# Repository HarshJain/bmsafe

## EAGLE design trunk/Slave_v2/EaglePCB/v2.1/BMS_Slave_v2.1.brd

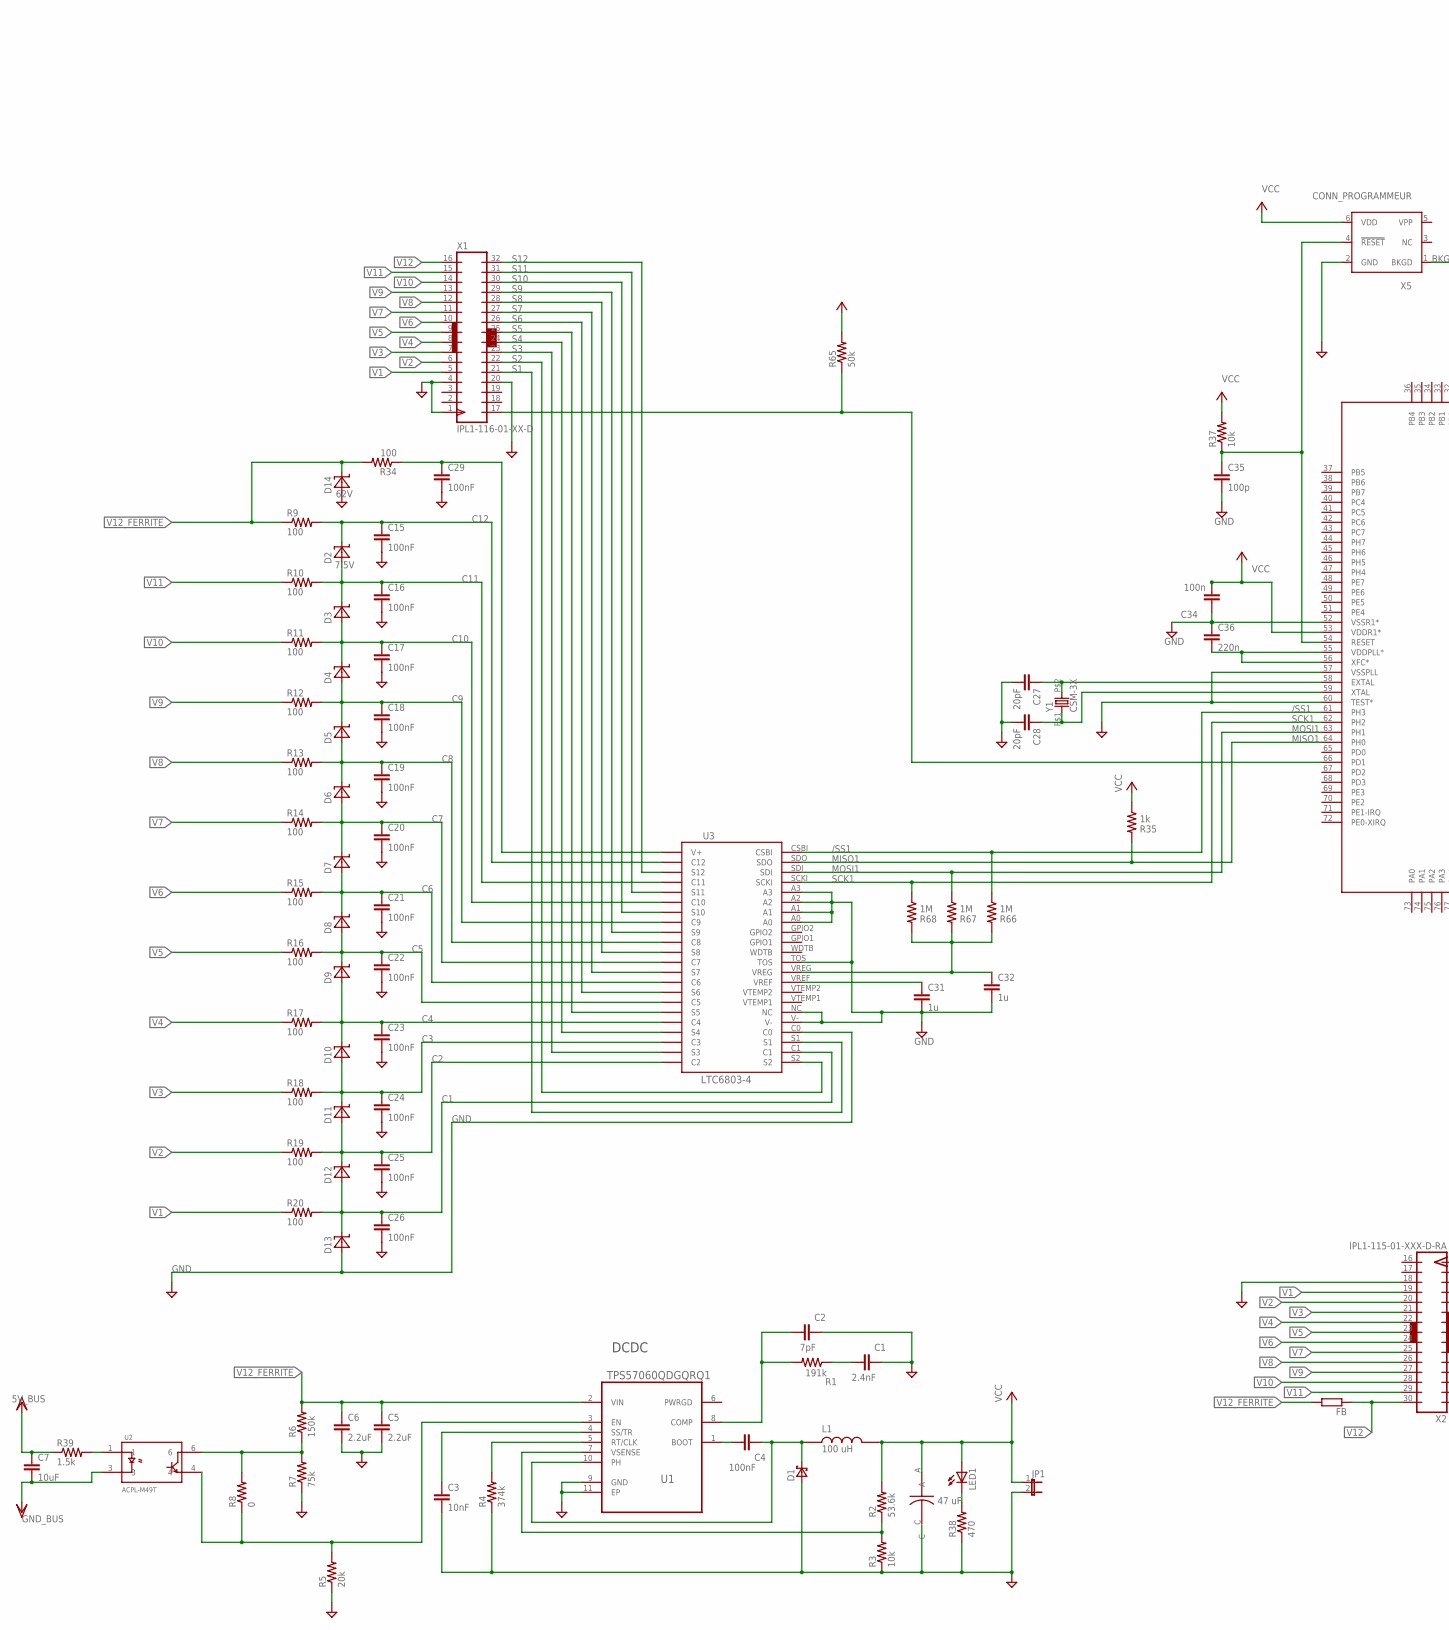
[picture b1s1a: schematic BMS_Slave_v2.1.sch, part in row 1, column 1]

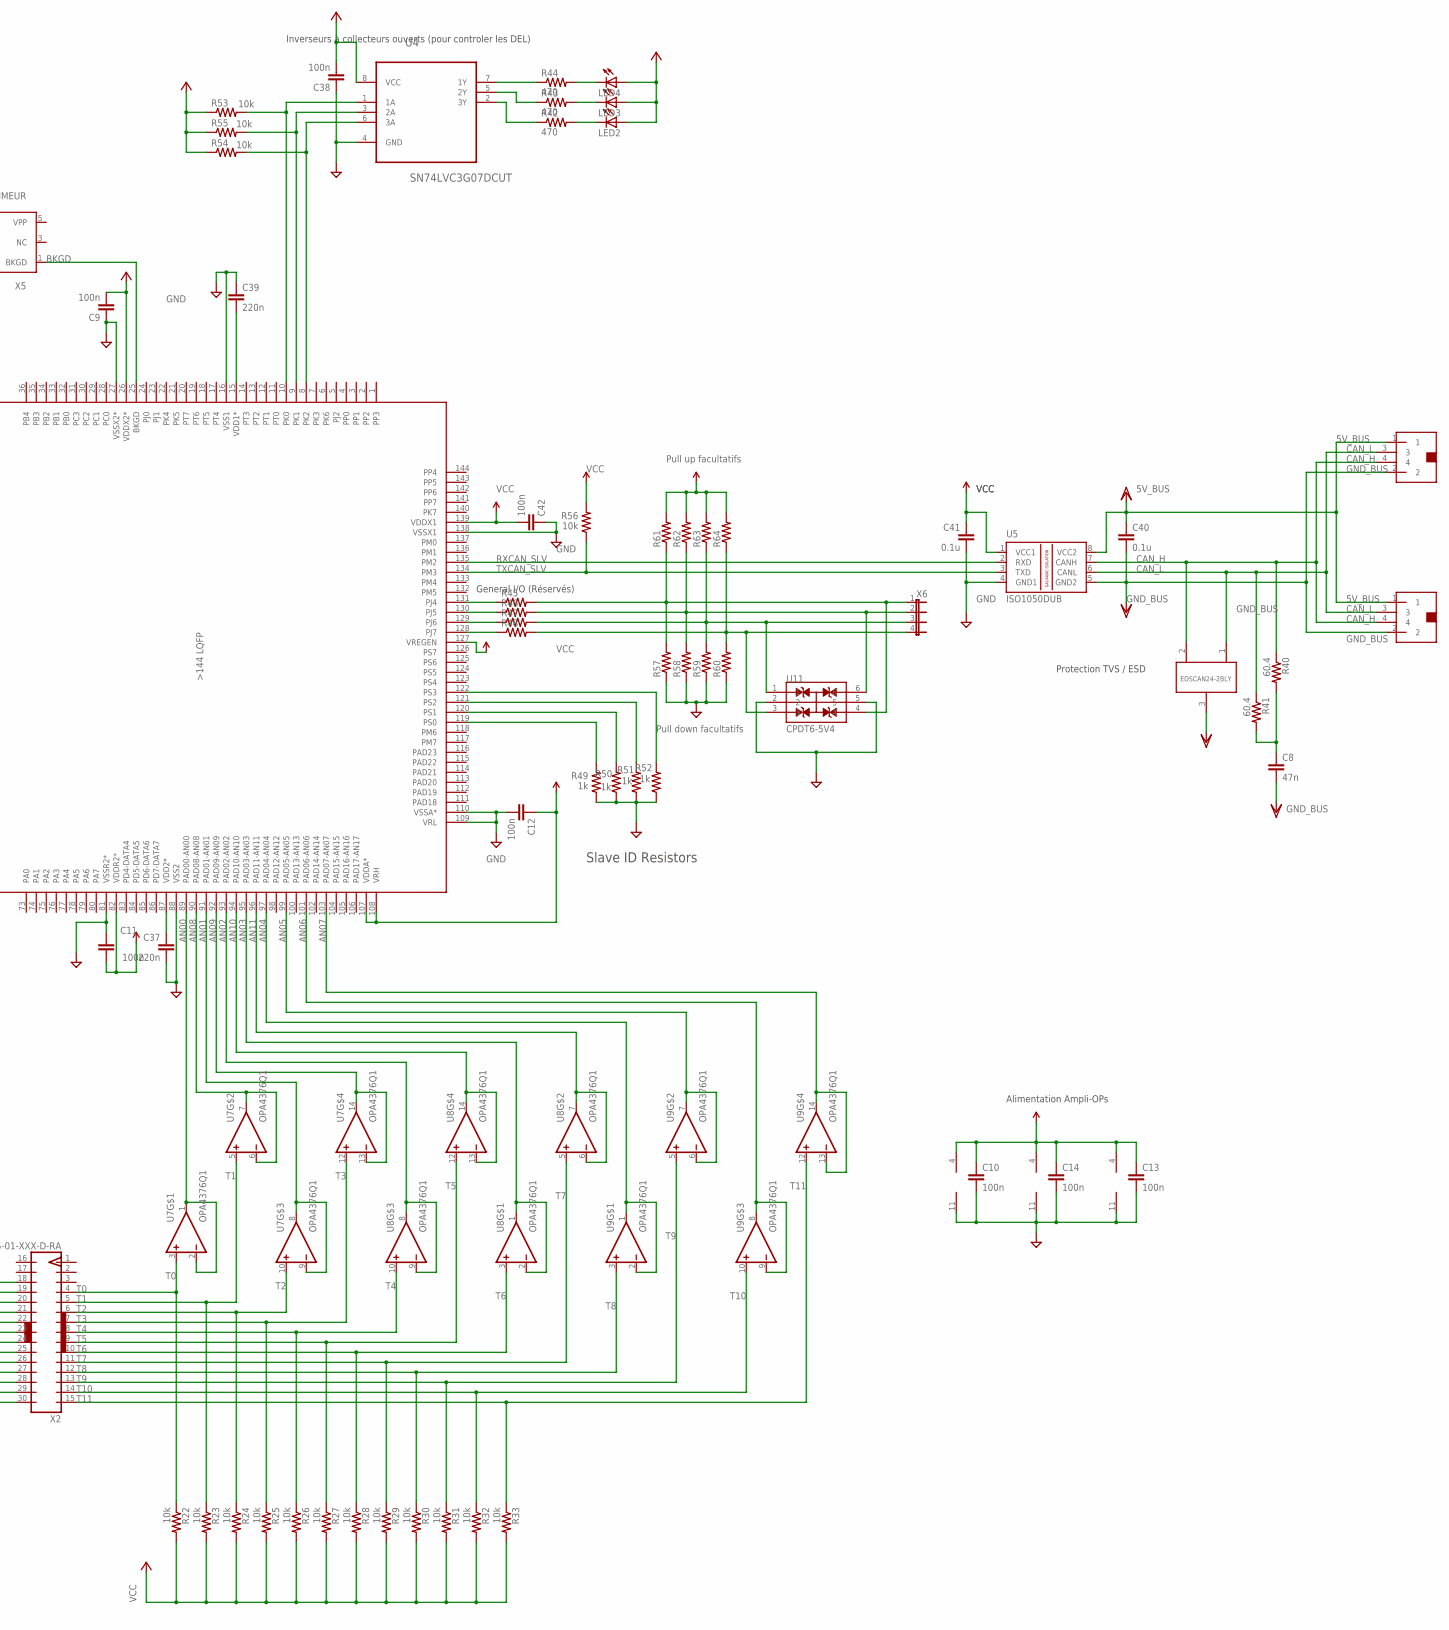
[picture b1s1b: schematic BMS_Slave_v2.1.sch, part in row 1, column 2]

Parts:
C1: 2.4nF; C0603
C2: 7pF; C0603
C3: 10nF; C0603
C4, C15, C16, C17, C18, C19, C20, C21, C22, C23, C24, C25, C26, C29: 100nF; C0603
C5, C6: 2.2uF; C3225
C7: 10uF; C0603
C8: 47n; C0603
C9, C10, C11, C12, C13, C14, C34, C38, C42: 100n; C0603
C27, C28: 20pF; C0603
C31, C32: 1u; C0603
C35: 100p; C0603
C36, C37, C39: 220n; C0603
C40, C41: 0.1u; C0603
C43: 47 uF; APXE_CONDENSATEUR
D1: BYS12-90GENERIC; DO214AC_ZENER
D2, D3, D4, D5, D6, D7, D8, D9, D10, D11, D12, D13, D14: DIODE_ZENER; SOD123
FB: R-EU_R0805; R0805
JP1: JP1E; JP1
L1: 100 uH; VLP8040T-101M
LED1, LED2, LED3, LED4: LED; 1206_LED
R1: 191k; R0603
R2: 53.6k; R0603
R3, R22, R23, R24, R25, R26, R27, R28, R29, R30, R31, R32, R33, R37, R53, R54, R55, R56: 10k; R0603
R4: 374k; R0603
R5: 20k; R0603
R6: 150k; R0603
R7: 75k; R0603
R8: 0; R0603
R9, R10, R11, R12, R13, R14, R15, R16, R17, R18, R19, R20, R34: 100; R0603
R35, R49, R50, R51, R52: 1k; R0603
R38, R42, R43, R44: 470; R0603
R39: 1.5k; R0603
R40, R41: 60.4; R0603
R45, R46, R47, R48, R57, R58, R59, R60, R61, R62, R63, R64: R-US_R0603; R0603
R65: 50k; R0603
R66, R67, R68: 1M; R0603
U1: TPS57060QDGQRQ1; SOP50P490X110-11N
U2: ACPL-M49T; SO5
U3: LTC6803-4
U4: SN74LVC3G07DCUT; SOP50P310X90-8N
U5: ISO1050DUB; DUB-R-PDSO-G8
U6: MC9S12XD-144; SQFP-S-20X20-144
U7, U8, U9: OPA4376Q1; TSSOP-14
U10: EDSCAN24-2BLY; SOT23-3
U11: CPDT6-5V4; SOT23-6
X1: IPL1-116-01-XX-D
X2: IPL1-115-01-XXX-D-RA
X3, X4: IPL1-102-01-XXX-D-RA
X5: CONN_PROGRAMMEUR; CONNECTEUR_PROGRAMMEUR
X6: JP4E; JP4
Y1: CSM-3X

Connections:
1: C2.1, R1.2, U1.8 (COMP)
5V_BUS: C7.1, C40.1, R39.1, U5.8 (VCC2), X3.1, X4.1
/SS1: R66.1, U3.CSBI, U6.61 (PH3)
AN00: U6.89 (PAD00-AN00), U7.1 (OUT), U7.2 (-IN)
AN01: U6.91 (PAD01-AN01), U7.8 (OUT), U7.9 (-IN)
AN02: U6.93 (PAD02-AN02), U8.8 (OUT), U8.9 (-IN)
AN03: U6.95 (PAD03-AN03), U8.1 (OUT), U8.2 (-IN)
AN04: U6.97 (PAD04-AN04), U9.1 (OUT), U9.2 (-IN)
AN05: U6.99 (PAD05-AN05), U9.6 (-IN), U9.7 (OUT)
AN06: U6.101 (PAD06-AN06), U9.8 (OUT), U9.9 (-IN)
AN07: U6.103 (PAD07-AN07), U9.13 (-IN), U9.14 (OUT)
AN08: U6.90 (PAD08-AN08), U7.6 (-IN), U7.7 (OUT)
AN09: U6.92 (PAD09-AN09), U7.13 (-IN), U7.14 (OUT)
AN10: U6.94 (PAD10-AN10), U8.13 (-IN), U8.14 (OUT)
AN11: U6.96 (PAD11-AN11), U8.6 (-IN), U8.7 (OUT)
BKGD: U6.25 (BKGD), X5.1 (BKGD)
C1: C26.1, D12.A, D13.C, R20.2, U3.C1
C2: C25.1, D11.A, D12.C, R19.2, U3.C2
C3: C24.1, D10.A, D11.C, R18.2, U3.C3
C4: C23.1, D9.A, D10.C, R17.2, U3.C4
C5: C22.1, D8.A, D9.C, R16.2, U3.C5
C6: C21.1, D7.A, D8.C, R15.2, U3.C6
C7: C20.1, D6.A, D7.C, R14.2, U3.C7
C8: C19.1, D5.A, D6.C, R13.2, U3.C8
C9: C18.1, D4.A, D5.C, R12.2, U3.C9
C10: C17.1, D3.A, D4.C, R11.2, U3.C10
C11: C16.1, D2.A, D3.C, R10.2, U3.C11
C12: C15.1, D2.C, R9.2, U3.C12
C44: C4.2, D1.C, L1.P$2, U1.10 (PH)
CAN_H: R40.1, U5.7 (CANH), U10.2, X3.4, X4.4
CAN_L: R41.1, U5.6 (CANL), U10.1, X3.3, X4.3
CSS: C3.1, U1.4 (SS/TR)
EXTAL: C27.1, U6.58 (EXTAL), Y1.P$2 (2)
GND: C1.2, C2.2, C3.2, C5.2, C6.2, C9.1, C10.2, C11.1, C12.2, C13.2, C14.2, C15.2, C16.2, C17.2, C18.2, C19.2, C20.2, C21.2, C22.2, C23.2, C24.2, C25.2, C26.2, C27.2, C28.2, C29.2, C31.2, C32.2, C34.1, C35.2, C36.1, C37.2, C38.1, C39.1, C41.2, C42.1, C43.C, D1.A, D13.A, D14.A, JP1.2, R3.1, R4.1, R5.1, R7.1, R38.1, R49.1, R50.1, R51.1, R52.1, R57.1, R58.1, R59.1, R60.1, U1.9 (GND), U1.11 (EP), U3.A0, U3.A1, U3.A2, U3.A3, U3.C0, U3.NC, U3.TOS, U3.V-, U4.4 (GND), U5.4 (GND1), U6.16 (VSS1), U6.27 (VSSX2*), U6.52 (VSSR1*), U6.57 (VSSPLL), U6.60 (TEST*), U6.81 (VSSR2*), U6.88 (VSS2), U6.109 (VRL), U6.110 (VSSA*), U6.138 (VSSX1), U7.11 (V-), U8.11 (V-), U9.11 (V-), U11.2, U11.5, X1.1, X1.4, X1.20, X2.18, X5.2 (GND)
GND_BUS: C7.2, C8.2, C40.2, U2.3, U5.5 (GND2), U10.3, X3.2, X4.2
MISO1: R35.2, U3.SDO, U6.64 (PH0)
MOSI1: R67.1, U3.SDI, U6.63 (PH1)
unnamed: C29.1, R34.1, U3.V+
unnamed: R39.2, U2.1
unnamed: C37.1, U6.87 (VDD2*)
unnamed: C31.1, U3.VREF
unnamed: C32.1, R66.2, R67.2, R68.2, U3.VREG
unnamed: C36.2, U6.55 (VDDPLL*), U6.56 (XFC*)
unnamed: R42.1, U4.2 (3Y)
unnamed: R49.2, U6.119 (PS0)
unnamed: R50.2, U6.120 (PS1)
unnamed: R51.2, U6.121 (PS2)
unnamed: R52.2, U6.122 (PS3)
unnamed: LED2.C, R42.2
unnamed: LED3.C, R43.2
unnamed: LED4.C, R44.2
unnamed: R44.1, U4.7 (1Y)
unnamed: R43.1, U4.5 (2Y)
unnamed: R65.1, U6.66 (PD1), X1.17
unnamed: R45.1, U6.131 (PJ4)
unnamed: C8.1, R40.2, R41.2
unnamed: R46.1, U6.130 (PJ5)
unnamed: R54.2, U4.6 (3A), U6.8 (PK2)
unnamed: R55.2, U4.3 (2A), U6.9 (PK1)
unnamed: R53.2, U4.1 (1A), U6.10 (PK0)
unnamed: C4.1, U1.1 (BOOT)
unnamed: R4.2, U1.5 (RT/CLK)
unnamed: R47.1, U6.129 (PJ6)
unnamed: R2.1, R3.2, U1.7 (VSENSE)
unnamed: LED1.C, R38.2
unnamed: R48.1, U6.128 (PJ7)
unnamed: R5.2, R8.1, U1.3 (EN), U2.4
unnamed: R6.1, R7.2, R8.2, U2.6
unnamed: R45.2, R57.2, R61.1, U11.4, X6.1
unnamed: R46.2, R58.2, R62.1, U11.6, X6.2
unnamed: R47.2, R59.2, R63.1, U11.1, X6.3
unnamed: R48.2, R60.2, R64.1, U11.3, X6.4
R59: C1.1, R1.1
RST: C35.1, R37.1, U6.54 (RESET), X5.4 (!RESET)
RXCAN_SLV: U5.2 (RXD), U6.135 (PM2)
S1: U3.S1, X1.21
S2: U3.S2, X1.22
S3: U3.S3, X1.23
S4: U3.S4, X1.24
S5: U3.S5, X1.25
S6: U3.S6, X1.26
S7: U3.S7, X1.27
S8: U3.S8, X1.28
S9: U3.S9, X1.29
S10: U3.S10, X1.30
S11: U3.S11, X1.31
S12: U3.S12, X1.32
SCK1: R68.1, U3.SCKI, U6.62 (PH2)
T0: R22.1, U7.3 (+IN), X2.4
T1: R23.1, U7.5 (+IN), X2.5
T2: R24.1, U7.10 (+IN), X2.6
T3: R25.1, U7.12 (+IN), X2.7
T4: R26.1, U8.10 (+IN), X2.8
T5: R27.1, U8.12 (+IN), X2.9
T6: R28.1, U8.3 (+IN), X2.10
T7: R29.1, U8.5 (+IN), X2.11
T8: R30.1, U9.3 (+IN), X2.12
T9: R31.1, U9.5 (+IN), X2.13
T10: R32.1, U9.10 (+IN), X2.14
T11: R33.1, U9.12 (+IN), X2.15
TXCAN_SLV: R56.1, U5.3 (TXD), U6.134 (PM3)
V1: R20.1, X1.5, X2.19
V2: R19.1, X1.6, X2.20
V3: R18.1, X1.7, X2.21
V4: R17.1, X1.8, X2.22
V5: R16.1, X1.9, X2.23
V6: R15.1, X1.10, X2.24
V7: R14.1, X1.11, X2.25
V8: R13.1, X1.12, X2.26
V9: R12.1, X1.13, X2.27
V10: R11.1, X1.14, X2.28
V11: R10.1, X1.15, X2.29
V12: FB.1, X1.16, X2.30
V12_FERRITE: C5.1, C6.1, D14.C, FB.2, R6.2, R9.1, R34.2, U1.2 (VIN)
VCC: C9.2, C10.1, C11.2, C12.1, C13.1, C14.1, C34.2, C38.2, C41.1, C42.2, C43.A, JP1.1, L1.P$1, LED1.A, LED2.A, LED3.A, LED4.A, R2.2, R22.2, R23.2, R24.2, R25.2, R26.2, R27.2, R28.2, R29.2, R30.2, R31.2, R32.2, R33.2, R35.1, R37.2, R53.1, R54.1, R55.1, R56.2, R61.2, R62.2, R63.2, R64.2, R65.2, U4.8 (VCC), U5.1 (VCC1), U6.26 (VDDX2*), U6.53 (VDDR1*), U6.82 (VDDR2*), U6.107 (VDDA*), U6.108 (VRH), U6.127 (VREGEN), U6.139 (VDDX1), U7.4 (V+), U8.4 (V+), U9.4 (V+), X5.6 (VDD)
VDD1: C39.2, U6.15 (VDD1*)
XTAL: C28.1, U6.59 (XTAL), Y1.P$1 (1)

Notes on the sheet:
Alimentation Ampli-OPs
Slave ID Resistors
Inverseurs à collecteurs ouverts (pour controler les DEL)
Protection TVS / ESD
DCDC
General I/O (Réservés)
Pull up facultatifs
Pull down facultatifs
62V
7.5V

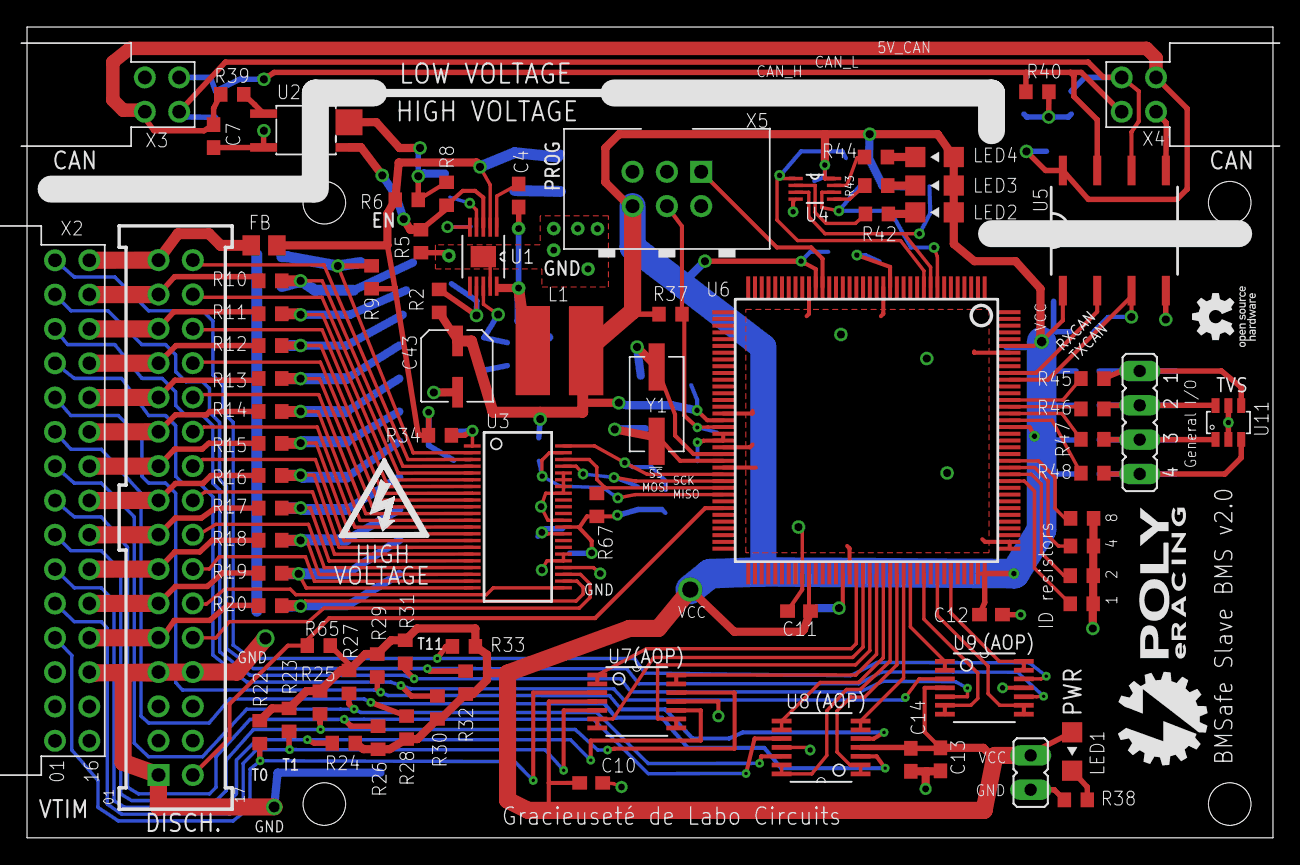
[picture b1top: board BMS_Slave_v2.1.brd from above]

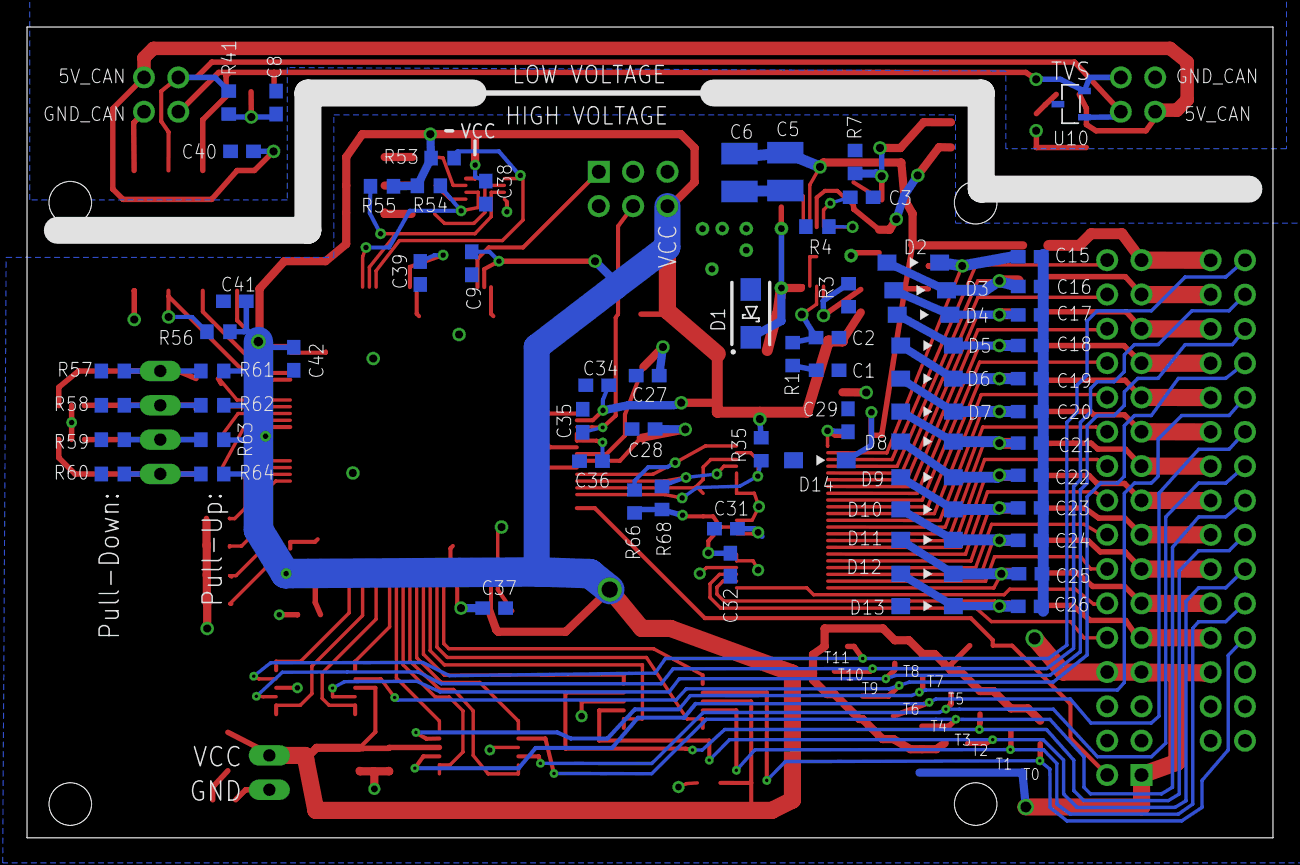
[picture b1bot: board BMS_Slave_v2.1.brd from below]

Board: 2 copper layers, 92.2 x 60.0 mm, 149 parts (68 on the bottom side), 117 nets.

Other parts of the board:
U$1: LOGO_HV
U$2: LOGO_ERACING
U$3: LOGO_OPEN_HARDWARE

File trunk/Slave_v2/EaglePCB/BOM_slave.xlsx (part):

Package custom
Vérifié + à commander |  |  |  | Facultatif ou variable : (REF)
Ne pas assembler |  |  |  | * même modèle avec un autre tag
Commandite
 |  |  |  |  |  |  |  |  |  |  | MQR : minimum quantity |  | 7 PCB
Référence | Do Not Place | Tag | Quantité (par esclave) | Numéro manufacturier | Value | Description | Supplier | Package | Prix Commande | Prix ($) | Commentaires | Lien | Total Qty | Qty Received | Received From | Qty to be ordered
U1 |  | DCDC | 1 | TPS57060-Q1 | - | Régulateur de tension | TI | MSOP10 (+PowerPAD) | 5.03 | 5.03 | Automotive | http://www.ti.com/product/tps57060-q1 | 7 | 3 | TI | 4
U2 |  | DCDC | 1 | ACPL-M49T | - | Optocoupleur | Newark | SO-5 | 4.76 | 4.76 | Automotive | http://www.digikey.ca/product-detail/en/ACPL-M49T-500E/516-2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 | 7 |  |  | 7
C1 |  | DCDC | 1 | GRM1885C1H242JA01D | 2.4 nF | Condensateur céramique | Digi-Key | 0603 | 0.16 | 0.16 | 50V, +-5% (Ccomp) | http://www.digikey.com/product-detail/en/GRM1885C1H242JA01D/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 | 7 |  |  | 7
C2 |  | DCDC | 1 | CGA3E2C0G1H070D080AA | 7 pF | Condensateur céramique | Digi-Key | 0603 | 0.1 | 0.1 | Automotive, 50V (Ccomp2) | http://www.digikey.com/product-detail/en/CGA3E2C0G1H070D080A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 | 7 |  |  | 7
C3 |  | DCDC | 1 | CGA3E2X7R1H103K080AD | 10 nF | Condensateur céramique | Digi-Key | 0603 | 0.28999999999999998 | 0.28999999999999998 | Automotive, 50V (Css) | http://www.digikey.ca/product-detail/en/CGA3E2X7R1H103K080AD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 | 7 |  |  | 7
C5,C6 |  | DCDC | 2 | CGA6N3X7R2A225K230AB | 2.2 uF | Condensateur découplage, X7R | Digi-Key | 1210 (3225 Metric) | 2.84 | 1.42 | Automotive, 100 V (Cin) | http://www.digikey.ca/product-detail/en/CGA6N3X7R2A225K230AB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 | 14 |  |  | 14
C43 |  | DCDC | 1 | APXE100ARA470ME61G | 47 uF | Condensateur électrolytique, découplage | Digi-Key | ~=E61 | 1.3 | 1.3 | 10V (Cout) | http://www.digikey.com/product-detail/en/APXE100ARA470ME61G/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 | 7 |  |  | 7
L1 |  | DCDC | 1 | VLP8040T-101M | 100 uH | Bobine | Digi-Key | Non Standard | 0.72 | 0.72 | +- 20%, 1 A, 330 mOhms | http://www.digikey.com/product-detail/en/VLP8040T-101M/445-6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 | 7 |  |  | 7
FB |  | DCDC | 1 | MPZ2012S300A | - | Ferrite | Digi-Key | 0805 | 0.12 | 0.12 |  | http://www.digikey.com/product-detail/en/MPZ2012S300A/445-15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 | 7 |  |  | 7
D1 |  | DCDC | 1 | BYS12-90-E3/TR | - | Schottky diode | Mouser | DO-214AC | 0.57999999999999996 | 0.57999999999999996 |  | http://www.digikey.com/product-detail/en/BYS12-90-E3%2FTR/BY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 | 7 |  |  | 7
R3 |  | DCDC* | 1 | CRCW060310K0FKEA | 10 kOhms | Résistance 1%, 1/8W | Digi-Key | 0603 | 8.1000000000000003E-2 | 8.1000000000000003E-2 | Automotive, MQ : 10 | http://www.digikey.com/product-detail/en/CRCW060310K0FKEA/54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 | 7 |  |  | 7
R2, R65 |  | DCDC | 2 | CRCW060353K6FKEA | 53.6 kOhms | Résistance 1%, 1/10 W | Digi-Key | 0603 | 0.16200000000000001 | 8.1000000000000003E-2 | Automotive, MQ : 10 | http://www.digikey.com/product-detail/en/CRCW060353K6FKEA/54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 | 14 |  |  | 14
R1 |  | DCDC | 1 | CRCW0603191KFKEA | 191 kOhms | Résistance 1%, 1/10 W | Digi-Key | 0603 | 8.1000000000000003E-2 | 8.1000000000000003E-2 | Automotive, MQ : 10 | http://www.digikey.com/product-detail/en/CRCW0603191KFKEA/54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 | 7 |  |  | 7
R4 |  | DCDC | 1 | CRCW0603374KFKEA | 374 kOhms | Résistance 1%, 1/10 W | Digi-Key | 0603 | 8.1000000000000003E-2 | 8.1000000000000003E-2 | Automotive, MQ : 10 | http://www.digikey.com/product-detail/en/CRCW0603374KFKEA/54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 | 7 |  |  | 7
R5 |  | DCDC | 1 | CRCW060320K0FKEA | 20 kOhms | Résistance EN | Digi-Key | 0603 | 0.04 | 0.04 | Automotive, MQ : 10 | http://www.digikey.com/product-detail/en/CRCW060320K0FKEA/54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 | 7 |  |  | 7
R6 |  | DCDC | 1 | CRCW0603150KFKEA | 150 kOhms | Résistance EN | Digi-Key | 0603 | 8.1000000000000003E-2 | 8.1000000000000003E-2 | Automotive, MQ : 10 | http://www.digikey.com/product-detail/en/CRCW0603150KFKEA/54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 | 7 |  |  | 7
R7 |  | DCDC | 1 | CRCW060375K0FKEA | 75 kOhms | Résistance EN | Digi-Key | 0603 | 8.1000000000000003E-2 | 8.1000000000000003E-2 | Automotive, MQ : 10 | http://www.digikey.com/product-detail/en/CRCW060375K0FKEA/54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 | 7 |  |  | 7
(R8) | x | DCDC* | 1 | RMCF0603ZT0R00 | 0 Ohms | Bypass pour activer le DCDC | Digi-Key | 0603 | 0 | 0.02 | Même que R36 | http://www.digikey.com/product-detail/en/RMCF0603ZT0R00/RMCF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 | 7 |  |  | 7
U4 |  | MCU | 1 | SN74LVC3G07-Q1 | - | Tripple buffer / driver (open collector) | TI | US8 (DCU) | 0.7 | 0.7 |  | http://www.ti.com/product/sn74lvc3g07-q1 | 7 | 3 | TI | 4
U6 |  | MCU | 1 | MC9S12XDP512MAG | - | Micro-contrôleur | Freescale | 144pin LQFP | 0 | 0 |  | http://www.digikey.ca/product-detail/en/MC9S12XDP512MAG/MC9S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 | 7 | 7 | Freescale | 0
C27-C28 |  | MCU | 2 | CC0603JRNPO9BN200 | 20 pF | Condensateur du crystal | Digi-Key | 0603 | 0.22 | 0.11 |  | http://www.digikey.ca/product-detail/en/CC0603JRNPO9BN200/31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 | 14 |  |  | 14
C35 |  | MCU | 1 | CGA3E2C0G1H101J080AA | 100 pF | Condensateur RESET (programmeur) | Digi-Key | 0603 | 0.12 | 0.12 | Automotive, 50V, 5% | http://www.digikey.ca/product-detail/en/CGA3E2C0G1H101J080AA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 | 7 |  |  | 7
C36,C37,C39 |  | MCU | 3 | CGA3E3X7R1V224K080AB | 220 nF | Condensateur céramique | Digi-Key | 0603 | 0.75 | 0.25 | Automotive 35V | http://www.digikey.ca/product-detail/en/CGA3E3X7R1V224K080AB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 | 21 |  |  | 21
R38,R42-R44 |  | MCU | 4 | RMCF0603JT470R | 470 Ohms | Résistance série (pour LED1-4) | Digi-Key | 0603 | 0.12 | 0.03 |  | http://www.digikey.ca/product-detail/en/RMCF0603JT470R/RMCF0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 | 28 |  |  | 28
R37,R53-R56 |  | MCU* | 5 | MCR03ERTJ103 | 10 kOhms | Pull up pour les LED drivers | Digi-Key | 0603 | 8.5000000000000006E-2 | 1.7000000000000001E-2 |  | http://www.digikey.com/product-detail/en/CRCW060310K0FKEA/54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 | 35 |  |  | 35
(R49-R52) | x | MCU* | 4 | MCR03ERTJ102 | 1 kOhms | Résistances pour l'ID des slaves | Digi-Key | 0603 | 3.4000000000000002E-2 | 1.7000000000000001E-2 |  | http://www.digikey.ca/product-detail/en/RMCF0603JT1K00/RMCF0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 | 28 |  |  | 28
LED3 |  | MCU | 1 | APT3216YC | - | LED jaune | Digi-Key | 1206 | 0.24 | 0.24 | 20 mA | http://www.digikey.com/product-detail/en/LTST-C150KSKT/160-1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 | 7 |  |  | 7
LED4 |  | MCU | 1 | LH N974-KN-1 | - | LED rouge | Digi-Key | 1206 | 0.13 | 0.13 | 20 mA | http://www.digikey.ca/product-detail/en/LTST-C150KRKT/160-14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 | 7 |  |  | 7
LED1, LED2 |  | MCU / Autre | 2 | LG N971-KN-1 | - | LED verte | Digi-Key | 1206 | 0.26 | 0.13 | 20 mA | http://www.digikey.com/product-detail/en/LTST-C150KGKT/160-1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 | 14 |  |  | 14
Y1 |  | MCU | 1 | ECS-160-20-3X-EN-TR | 16 MHz | Crystal | Digi-Key | HC49 | 0.72 | 0.72 |  | http://www.digikey.ca/product-detail/en/ECS-160-20-3X-EN-TR/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 | 7 |  |  | 7
U5 |  | CAN | 1 | ISO1050 | - | Isolated CAN Transceiver | Digi-Key | SOP-8 | 5.93 | 5.93 |  | http://www.digikey.ca/product-detail/en/ISO1050DUBR/296-2481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 | 7 | 2 | TI | 5
U10 |  | CAN | 1 | ESDCAN24-2BLY | - | Protection TVS/ESD pour le CAN | Digi-Key | SOT23 | 0.69 | 0.69 |  | http://www.digikey.ca/product-detail/en/ESDCAN24-2BLY/497-13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 | 7 |  |  | 7
C7 |  | CAN | 1 | C1608X5R1A106M080AC | 10 uF | Condensateur optocoupleur | Digi-Key | 0603 | 0.53 | 0.53 |  | http://www.digikey.ca/product-detail/en/C1608X5R1A106M080AC/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 | 7 |  |  | 7
C8 |  | CAN | 1 | CC0603KRX7R8BB473 | 47 nF | Condensateur bus CAN | Digi-Key | 0603 | 0.11 | 0.11 | Terminaison bus CAN | http://www.digikey.ca/product-detail/en/CGA3E2X5R1H473K080AA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 | 7 |  |  | 7
R39 |  | CAN* | 1 | CRCW060310K0FKEA | 10 kOhms | Résistance Optocoupleur | Digi-Key | 0603 | 8.1000000000000003E-2 | 8.1000000000000003E-2 | Automotive, MQ : 10 | http://www.digikey.com/product-detail/en/CRCW060310K0FKEA/54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 | 7 |  |  | 7
(R40,R41) | x | CAN | 2 | RC1608F60R4CS | 60.4 Ohms | Résistances de terminaison du bus CAN | Digi-Key | 0603 | 0.13 | 0.13 |  | http://www.digikey.ca/product-detail/en/RC1608F60R4CS/1276-4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 | 14 |  |  | 14
U3 |  | Tensions | 1 | LTC6803-4 | - | Puce de mesure des tensions | Linear | SSOP-48 | 23.9 | 23.9 |  | http://www.linear.com/product/LTC6803-2 | 7 | 10 | Linear | -3
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
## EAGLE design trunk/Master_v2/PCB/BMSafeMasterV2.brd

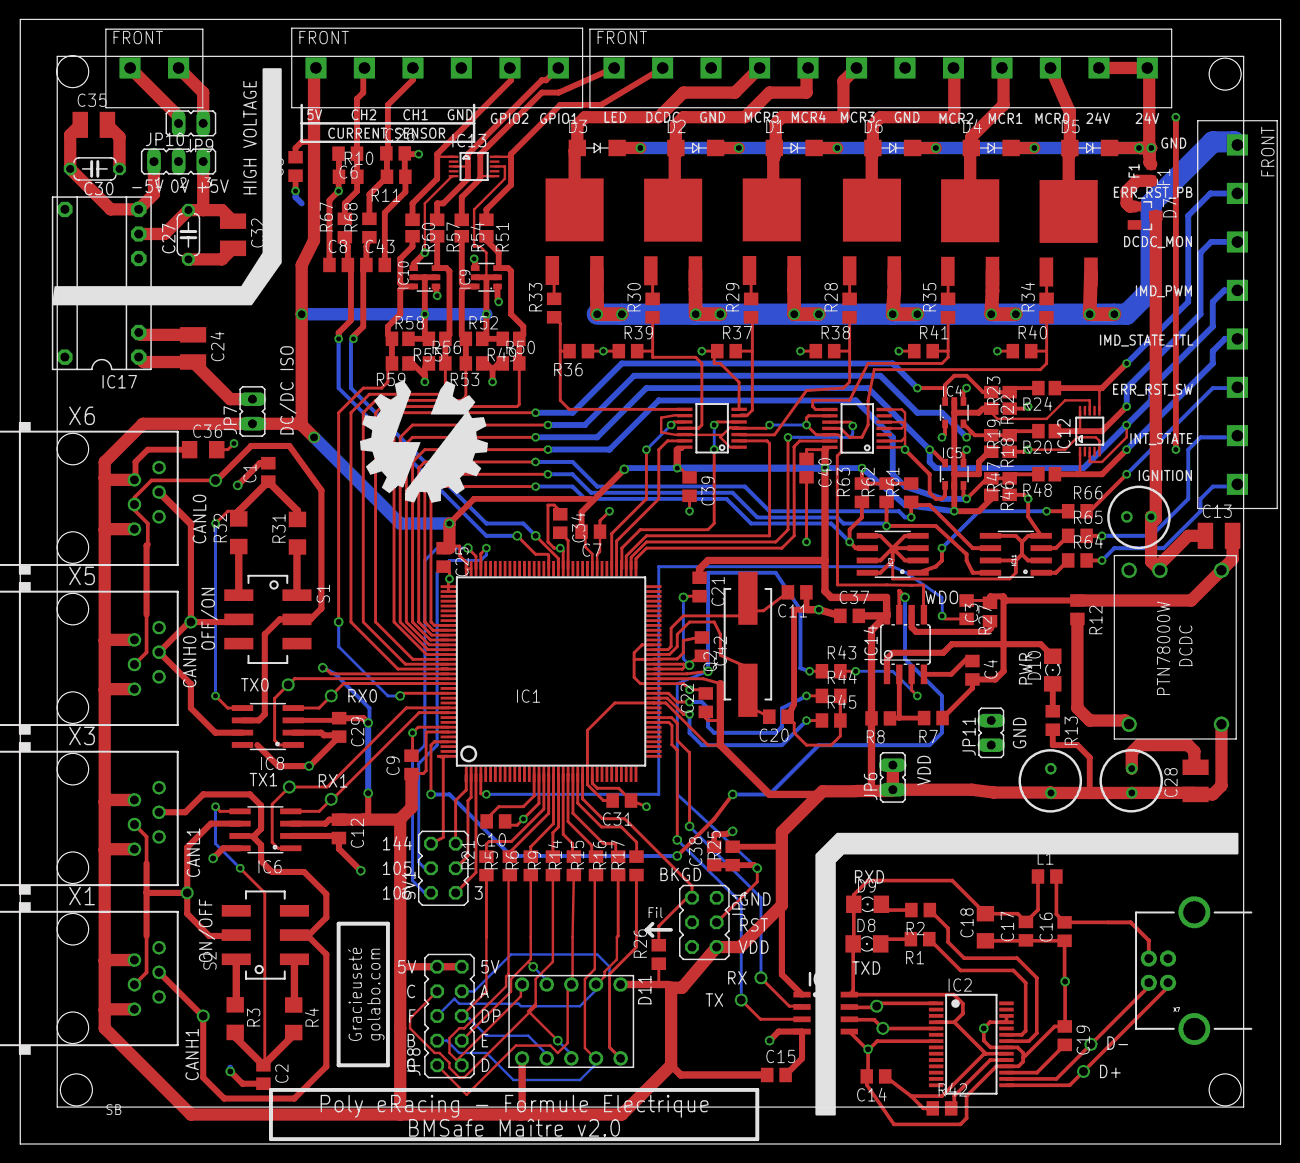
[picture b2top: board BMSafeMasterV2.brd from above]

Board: 2 copper layers, 130.0 x 116.0 mm, 172 parts (0 on the bottom side), 132 nets.

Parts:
C1, C2, C5, C6, C26: 47n; C0805
C3, C4, C7, C9, C12, C17, C19, C21, C22, C25, C29, C31, C37, C39, C40: 100n; C0805
C8, C43: LPF; C0805
C10, C34: 220nF; C0805
C11, C20: 18p; C0805
C13, C24, C28, C32, C35: 2.2u; C1210
C14, C15: 0.047u; C0805
C16: 10n; C0805
C18, C36: 4.7u; C1206
C23, C33: 100u; EEU-FM1E101
C27, C30: 1u; C050-024X044
C38: 100p; C0805
C41: 470u; EEU-FM1E101
C42: 220n; C0805
D1, D2, D3, D4, D5, D6: GF1; SMA-DO214AC
D7: BAT54; SOT23
D8, D9, D10: 1206
D11: LA-401AD; LA-401
F1: 467; 0603
IC1: MC9S12XF-144; SQFP-S-20X20-144
IC2: FT232RL; SSOP28
IC3: ADUM1201; SOIC
IC4, IC5, IC9, IC10: SDM10M45SD; SOT-26
IC6, IC8: TJA1040; SO8
IC7, IC11: ILD213T; SO08
IC12, IC13: CM1213-08MR; MSOP10
IC14: WATCHDOG; SOIC08
IC15, IC16: SN74HC08; TSSOP14
IC17: DCP0115P; DIL14/7
IC18: DCDCMAITRE_HOLES
JP1: JP3Q
JP2, JP3, JP4, JP5: STAND-OFF
JP6, JP7, JP9, JP11: JP1
JP8: JP5Q
JP10: JP2
L1: MYDEVICE; C0805
Q1, Q3, Q4, Q5, Q6, Q7: IRLR014; TO-252
Q2: CSM-7X
R1, R2, R13: 475; R0805
R3, R4, R31, R32: 60.4; R1206
R5, R6, R9, R14, R15, R16, R17: 10K; R0805
R7, R8: 1M; R0805
R10, R11: 100k; R0805
R12: 21k; R0805
R18, R19, R21, R22, R23, R25, R26, R27, R36, R37, R38, R39, R40, R41, R42, R46, R47, R49, R50, R52, R53, R55, R56, R58, R59: 10k; R0805
R20, R24, R48, R51, R54, R57, R60: 2.5k; R0805
R28, R29, R30, R33, R34, R35: 1k; R0805
R43: 0; R0805
R44, R45: 4.7k; R0805
R61, R62, R63, R64, R65, R66: TBD; R0805
R67, R68: LPF; R0805
S1, S2: SWITCH_DPDT; DPDT
SV1: JP3Q
X1, X3, X5, X6: RJ11-2L-B; RJ11-NO_SHIELD
X2: 282836-6
X4: 1-282836-2
X7: USBPTH; USB-B-PTH
X8: 282836-2
X9: 282836-8

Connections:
5V_MST: C5.2, C7.2, C9.1, C12.1, C15.1, C21.1, C22.1, C23.1, C25.1, C28.1, C29.1, C31.2, C33.1, C36.1, C37.2, C39.1, C40.1, D11.1, D11.6, IC1.26, IC1.48, IC1.53, IC1.82, IC1.107, IC1.108, IC1.127, IC1.139, IC3.1, IC4.2, IC4.5, IC5.2, IC5.5, IC6.3, IC8.3, IC9.2, IC9.5, IC10.2, IC10.5, IC12.8, IC13.8, IC14.8, IC15.14, IC16.14, IC18.5, JP1.6, JP6.1, JP6.2, JP7.1, JP8.9, JP8.10, R8.2, R13.2, R18.2, R22.2, R25.2, R26.1, R46.2, R49.2, R52.2, R55.2, R58.2, R61.2, R62.2, R63.2, X1.2, X1.6, X2.CON01, X3.2, X3.6, X5.2, X5.6, X6.2, X6.6
5V_USB: C14.1, C17.2, C18.2, D8.A, D9.A, IC2.4, IC2.20, IC3.8, L1.1, R42.1
+5V_ISO: C27.2, C32.1, IC17.6, JP10.3
-5V_ISO: C30.2, C35.1, IC17.7, JP10.1
AN00: C43.1, IC1.89, R68.1
AN00_C: C26.1, R11.2, R68.2, X2.CON03
AN01: C8.2, IC1.91, R67.1
AN01_C: C6.1, R10.2, R67.2, X2.CON02
AN16: IC1.105, SV1.4
AN17: IC1.106, SV1.2
B: D11.9, JP8.4, R15.1
BKGD: IC1.25, JP1.1, R26.2
C: D11.8, JP8.8, R9.1
CANH0: IC8.7, S1.5, X5.3, X6.3
CANH1: IC6.7, S2.5, X1.3, X3.3
CANL0: IC8.6, S1.2, X5.4, X6.4
CANL1: IC6.6, S2.2, X1.4, X3.4
D: D11.5, JP8.1, R5.1
DCDC_MONITOR: IC1.122, IC4.3, R18.1, R19.2, R20.2
DCDC_MONITOR_C: IC12.10, R20.1, X9.CON03
DCDC_MOSFET: IC1.124, IC9.3, R49.1, R50.2, R51.2
DCDC_MOSFET_C: IC13.10, R51.1, X4.CON2
DP: D11.7, JP8.5, R21.1
E: D11.4, JP8.3, R6.1
ERR_RST_DASH: IC1.117, IC7.6, R63.1
ERR_RST_DASH_C: R66.2, X9.CON06
ERR_RST_PUSHBUTTON: IC1.123, IC4.6, R22.1, R23.2, R24.2
ERR_RST_PUSHBUTTON_C: IC12.6, R24.1, X9.CON02
EXTAL: C20.2, IC1.58, Q2.1
F: D11.2, JP8.6, R16.1
G: D11.3, JP8.2, R14.1
GM2: IC15.3, R28.1, R38.2
GM3: IC15.6, R29.1, R37.2
GND_MOSFET: Q1.P$3, Q3.P$3, Q4.P$3, Q5.P$3, Q6.P$3, Q7.P$3, X9.CON01
GND_MST: C1.2, C2.2, C3.2, C4.2, C5.1, C6.2, C7.1, C8.1, C9.2, C10.1, C11.1, C12.2, C13.2, C15.2, C20.1, C22.2, C23.2, C24.1, C25.2, C26.2, C28.2, C29.2, C31.1, C33.2, C34.1, C36.2, C37.1, C38.2, C39.2, C40.2, C41.2, C42.1, C43.2, D10.C, IC1.16, IC1.27, IC1.52, IC1.57, IC1.60, IC1.81, IC1.88, IC1.109, IC1.110, IC1.138, IC3.4, IC4.1, IC4.4, IC5.1, IC5.4, IC6.2, IC6.8, IC7.2, IC7.3, IC7.4, IC7.5, IC7.7, IC7.8, IC8.2, IC8.8, IC9.1, IC9.4, IC10.1, IC10.4, IC11.2, IC11.4, IC11.5, IC11.7, IC12.5, IC13.5, IC14.1, IC15.7, IC16.1, IC16.2, IC16.4, IC16.5, IC16.7, IC17.2, IC18.1, JP1.2, JP11.1, JP11.2, R7.1, R10.1, R11.1, R12.1, R19.1, R23.1, R27.1, R36.1, R37.1, R38.1, R39.1, R40.1, R41.1, R44.2, R45.2, R47.1, R50.1, R53.1, R56.1, R59.1, X1.1, X1.5, X2.CON04, X3.1, X3.5, X4.CON3, X4.CON7, X5.1, X5.5, X6.1, X6.5
GND_USB: C14.2, C16.1, C17.1, C18.1, C19.1, IC2.7, IC2.18, IC2.21, IC2.25, IC2.26, IC3.5, X7.GND
GPIO1: IC1.126, IC10.3, R55.1, R56.2, R57.2
GPIO1_C: IC13.3, R57.1, X2.CON06
GPIO2: IC1.131, IC10.6, R58.1, R59.2, R60.2
GPIO2_C: IC13.1, R60.1, X2.CON05
HV_GND: C27.1, C30.1, C32.2, C35.2, IC17.5, JP10.2
IGNITION: IC1.119, IC11.6, R61.1
IGNITION_C: R64.2, X9.CON08
IMD_STATE_PWM: IC1.121, IC5.6, IC12.3, X9.CON04
IMD_STATE_TTL: IC1.120, IC5.3, R46.1, R47.2, R48.2
IMD_STATE_TTL_C: IC12.1, R48.1, X9.CON05
INTERLOCK_STATE: IC1.118, IC11.8, R62.1
INTERLOCK_STATE_C: R65.2, X9.CON07
LED_BMS_DASH: IC1.125, IC9.6, R52.1, R53.2, R54.2
LED_BMS_DASH_C: IC13.6, R54.1, X4.CON1
MCR0: D5.A, Q6.P$4, X4.CON10
MCR1: D4.A, Q7.P$4, X4.CON9
MCR2: D6.A, Q5.P$4, X4.CON8
MCR3: D1.A, Q4.P$4, X4.CON6
MCR4: D2.A, Q3.P$4, X4.CON5
MCR5: D3.A, Q1.P$4, X4.CON4
unnamed: IC14.2, R7.2, R8.1
unnamed: D11.10, JP8.7, R17.1
unnamed: C4.1, IC14.4
unnamed: IC11.1, R64.1
unnamed: C3.1, IC14.6
unnamed: D10.A, R13.1
unnamed: IC11.3, R65.1
unnamed: IC16.11, R34.1, R40.2
unnamed: Q6.P$1, R34.2
unnamed: JP9.2, X8.CON1
unnamed: JP9.1, X8.CON2
unnamed: IC16.8, R35.1, R41.2
unnamed: Q7.P$1, R35.2
unnamed: Q1.P$1, R33.2
unnamed: C2.1, IC6.5, R3.2, R4.2
unnamed: R3.1, S2.1
unnamed: R4.1, S2.4
unnamed: IC2.15, X7.D+
unnamed: IC2.16, X7.D-
unnamed: IC2.23, R1.1
unnamed: D8.C, R1.2
unnamed: IC2.22, R2.1
unnamed: D9.C, R2.2
unnamed: C19.2, IC2.17
unnamed: IC15.8, R33.1, R36.2
unnamed: C1.1, IC8.5, R31.2, R32.2
unnamed: IC15.11, R30.1, R39.2
unnamed: Q3.P$1, R30.2
unnamed: R31.1, S1.1
unnamed: R32.1, S1.4
unnamed: Q4.P$1, R29.2
unnamed: Q5.P$1, R28.2
unnamed: IC2.19, R42.2
unnamed: IC1.50, R44.1
unnamed: IC1.49, R45.1
unnamed: D7.1, F1.2
unnamed: IC7.1, R66.1
PA0: IC1.73, IC16.13
PA1: IC1.74, IC16.10
PA2: IC1.75, IC15.2
PA3: IC1.76, IC15.5
PA4: IC1.77, IC15.13
PA5: IC1.78, IC15.10
PJ0: IC1.24, R17.2
PJ1: IC1.23, R16.2
PK4: IC1.22, R15.2
PK5: IC1.21, R14.2
PP1: IC1.3, SV1.1
PP2: IC1.2, SV1.3
PP3: IC1.1, SV1.5
PP4: IC1.144, SV1.6
PP7: IC1.141, IC14.7
PT4: IC1.17, R21.2
PT5: IC1.18, R5.2
PT6: IC1.19, R6.2
PT7: IC1.20, R9.2
RES_N: IC14.3, R43.2
RST: C38.1, IC1.54, JP1.4, R25.1, R43.1
RXCAN0: IC1.129, IC8.4
RXCAN1: IC1.135, IC6.4
RXD_MST: IC1.45, IC3.2
RXD_USB: IC2.5, IC3.6
TXCAN0: IC1.128, IC8.1
TXCAN1: IC1.134, IC6.1
TXD_MST: IC1.44, IC3.3
TXD_USB: IC2.1, IC3.7
VDD: C34.2, IC1.87
VDD1: C10.2, IC1.15
VDDPLL: C21.2, C42.2, IC1.55, IC1.56
VIN: D1.K, D2.K, D3.K, D4.K, D5.K, D6.K, F1.1, X4.CON11, X4.CON12
VIN_F: C13.1, C41.1, D7.3, IC18.2
VOADJUST: IC18.4, R12.2
VS: C24.2, IC17.1, JP7.2
VUSB: C16.2, L1.2, X7.VBUS
WDO: IC1.4, IC14.5, IC15.1, IC15.4, IC15.9, IC15.12, IC16.9, IC16.12, R27.2
XTAL: C11.2, IC1.59, Q2.2

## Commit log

2011-05-03 Initial directory structure.
2011-05-03 Version 1.0.0
2011-05-03 Created wiki page through web user interface.
2011-05-03 Edited wiki page Preview through web user interface.
2011-07-26 I forgot to commit this folder...
2011-10-12 Added battery box CAD. Added material list (cahier de charge de préparation) for module assembly
2011-10-12 Added real battery box drawing
2012-01-29 Adding the source...
2012-03-19 - Files MCUinit.ca and MCUinit.h were empty, replaced with most recent versions. - Removed folder SPI_linear_Data which was not used. - Removed big.hwl which is a workspace configuration file.
2012-03-19 - Deleted the folder SPI_linear_Data which is not used and big.hwl... take 2.
2012-03-21 Update du slave en tenant compte des corrections de Maxime Lavigne, je crois.
2012-04-17 Ajout d'une fonction qui gère le relais de décharge, sur le port M.
2012-05-12 Nombreux changements, majoritairement pour la lisibilité du code. Ajout également d'un processus de reprise de communication avec la puce LTC6802-2 advenant une coupure dans le lien SPI.
    Non testé dans cette version:
    - Réception de messages CAN et leur traitement.
2012-05-12 Bon j'ai pas encore le tour avec les commit...
2012-05-30 Ajout d'un message CAN pour l'envoi de la version du firmware. Ajout du mode veille du CPU, ADC et SPI.
2012-05-30 Beaucoup de choses!!! Ménage du code pour ne garder que l'essentiel pour la compétition 2012.
2012-08-31 Version fonctionnelle de la competition FSG 2012
2012-08-31 Version fonctionnelle a la competition FSG 2012. Version utilisant le microcontroleur original, soit le MC9S12XEP100MAL.
2012-08-31 Version qui peut etre programmee sur le microcontroleur MC9S12XDP512. La lecture du courant n'est pas encore fonctionnelle. Il ne manque que quelques changements au code.
2012-12-10 Cleanup général du code.
    * Reformattage du code pour le rendre consistant.
    * Modification de tous les types ambigus pour leur version précise.
2012-12-10 Modification préalable au changement de module can.
    * Ajouter dans CANSlave.c du code pour un traitement
    par message des envois. Pour abstraire tous les
    détails d'envoie que quelqu'un voulant utiliser
    le CAN n'a pas besoin de savoir. (Il n'est pas
    en fonction par contre, j'ai laisser l'ancien
    jusqu'à ce que je puisse tester live le switch).
2013-07-25 Version 2.0.0 Utilisee pour la competition a Lincoln en juin 2013
    Adaptation du code au PCB version 2 du BMS master (avec MCU correspondant)
    - Changement du nom des pins dans defines.h et relays.h et la configuration de ces pins
    Ajout d'une fonctionnalite pour ignorer certaines sondes de temperatures qui donnent une lecture erronee
    - main.c : nouveau tableu (gCellIgnoreTemp) contenant le numero des cellules dont la sonde est ignoree
    Ajout d'un delais avant l'activation de l'erreur cellMinVoltage (declenchee inutilement lors de l'acceleration)
    - MCUinit.c : changements dans l'interruption iPIT1_safety_check()
2015-01-25 Master update : - BMS Slave hardware v2 - BMS Slave software v2 - BMS Master hardware v2 (was already on the SVN however) - BMS Master software v2
    This is a major update pushing the last version of hardware and software of the BMS BMSafe project. There have been a lots of improvements in the software, re-organization of functions, clarification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
    The subsequent updates will mostly be for documentation. There is a big lack in do
2015-03-12 Testing html display on googlecode.
2015-03-29 Migrating wiki contents from Google Code
